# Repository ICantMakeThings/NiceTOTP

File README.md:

# NiceTOTP 

## Wiki

- [What is NiceTOTP?](#what-is-nicetotp)
- [But Why?](#but-why)
- [Hardware](#hardware-is)
- [Usage](#usage)
	- [UI](Docs/ui.md)
- [Installation](#installation)
	- [Standard installation](#standard-installation)
	- [Protected installation](#protected-installation)
- [More Info](#more-info)
- [Build protected from source](Docs/build-protected-from-source.md)

# What is NiceTOTP?

Time-based one-time password (TOTP). aka: 2FA! 
A alternetive to [Authy](https://www.authy.com/) / [Google Authenticator](https://play.google.com/store/apps/details?id=com.google.android.apps.authenticator2). 

Full offline, Air Gapped. And Standalone once all Keys have been added.

TOTP keys and other FS are stored in an AES-256-GCM encrypted vault, with a key derived from the passcode using PBKDF2-HMAC-SHA-256. Vaults use a random starting IV followed by monotonically increasing IVs.

A four-digit passcode is still vulnerable to offline guessing if an attacker extracts the flash. Use a longer, unpredictable numeric passcode; a lengt of 13 can make a attacker wait up to 8 years on the most common GPU* 

[Video here](https://www.youtube.com/watch?v=sLiadPXk7rc)

## But Why?? 

There are a few reasons why I made this device, mainly to lose dependence of my phone. But not just, What if your phone breaks, bricks, or something else? I rather have lots of devices that don't depend on eachother rather than a all in one for that reason, plus most "universal" stuff performs worse than a specific device for that single function. As of right now, I'd say it's almost complete (enough to daily drive), possibly a few more hardware security features, maybe UI polishing, fixing any bugs i haven't found yet and should be perfect. The cost is ~£6 excluding 3D printing.

## Hardware is:
+ Nice!Nano: [AliExpress Link](https://s.click.aliexpress.com/e/_omlmCuu)
+ DS3231 RTC: [AliExpress Link](https://s.click.aliexpress.com/e/_omVV4ia)
+ 0.96Inch Display: [AliExpress Link](https://s.click.aliexpress.com/e/_ooXwYgq)
+ 6*6 Silicone Switch: [AliExpress Link](https://s.click.aliexpress.com/e/_oDcs8Wa)
+ 3D [model](https://www.thingiverse.com/thing:7087241)

*Note: These are referral links. If you purchase through it, I earn a commission at no extra cost to you.*

# Usage
#### Use the [NiceTOTP-ConfiguratorNext](https://github.com/ICantMakeThings/NiceTOTP/releases)  (Firmware update doesnt work rn*)
#### or you can use serial commands:
- `setunixtime` example: `setunixtime 1751925355` 
- The first `setunixtime` stores the real time for future auto-calibration which after 30 days it will compensate for any drift in the DS3231.
- `manualcalibration <offset>` example: `manualcalibration 3` sets the DS3231 aging register from -128 to 127 and locks automatic calibration
- `lockcalibration` stops auto-calibration
- `unlockcalibration` turns back on auto-calibration
- `getcalibration` reports the aging offset, baseline timestamp, and lock state
- `clearcalibration` clears the aging correction and removes the stored calibration baseline
- `add <username> <base32secret>` example: `add test JBSWY3DPEHPK3PXP` ([Compare](https://totp.danhersam.com/?secret=JBSWY3DPEHPK3PXP))
- `list`
- `del <GetTheIDFromListCommand>` example: `del 1`
- `factoryreset` (Power cycle after)

# Installation

### Standard installation

If you don't care about proper security*, download the [NiceTOTP-ConfiguratorNext](https://github.com/ICantMakeThings/NiceTOTP/releases) and use the unsigned `NiceTOTP-V1x.uf2` firmware.

**Or if you just want to test the device without commiting to the protected bootloader / hassle with setting it up or not owning a ST-Link*

+ Or Drag and drop the .UF2 onto the nicenano drive when doubble clicking reset (short rst pin with usbc sheild tapping twice quickly)

### Protected installation
- Download `Signed.zip` from latest release, and follow
[Protected installation](Docs/build-protected-from-source.md) (Also includes installing from source)

# More Info

+ In 2 months the RTC drifted 8s forward. (Now there is a calibration feature, so should be better, to be commented on further.)

+ Battery seems to last about 1 year with a 1000mAh Battery.

+ Make sure not to let it discharge as it will go in a soft brick, to unbrick you just press rst 

#### GPU* 

- The algorythm is **50,000 PBKDF2** and the number is the expected value which is ½ of the worse-case scenario.
- It is based on cracking it with a NVIDIA GeForce RTX 3060 as its the most common GPU based on [Steam Hardware & Software Survey: August 2026.](https://store.steampowered.com/hwsurvey/En)
- It is recommended to have a pin of at least 13 Charicters
- You can have a look on [this webiste](https://jmrp.io/tools/pin-brute-force-calculator/) to test around different hardware, make sure PBKDF2 iterations is set to `50000`

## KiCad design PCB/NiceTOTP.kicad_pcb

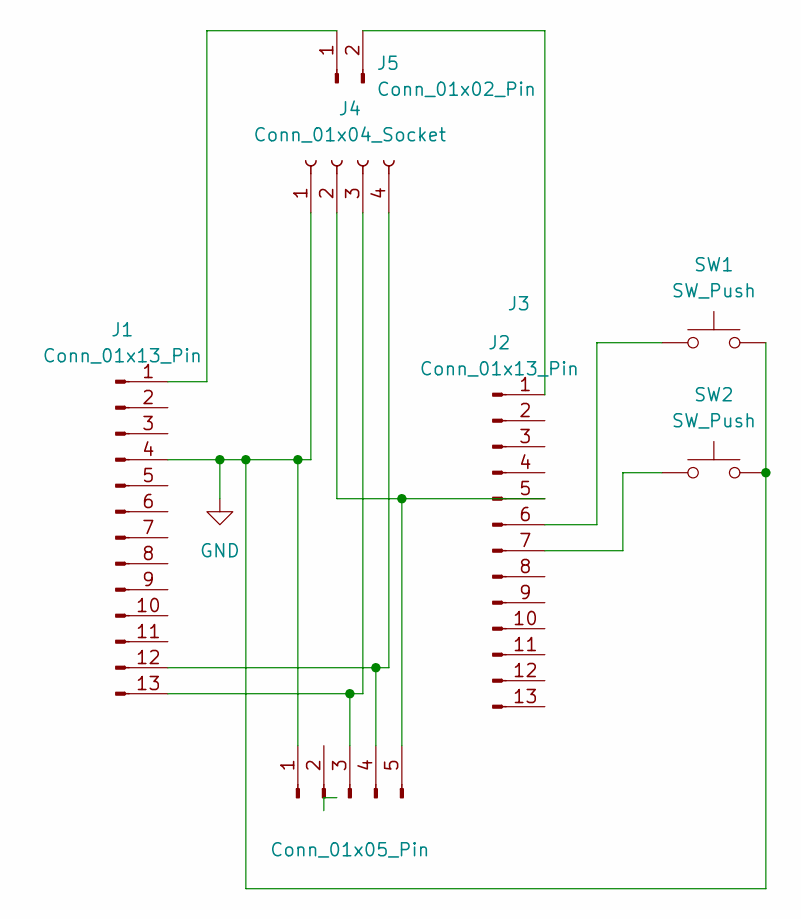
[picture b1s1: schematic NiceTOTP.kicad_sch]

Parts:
J1, J2: Conn_01x13_Pin; PinHeader_1x13_P2.54mm_Vertical
J3: Conn_01x05_Pin; PinHeader_1x05_P2.54mm_Vertical
J4: Conn_01x04_Socket; PinHeader_1x04_P2.54mm_Vertical
J5: Conn_01x02_Pin; PinHeader_1x02_P2.54mm_Vertical
SW1, SW2: SW_Push; SW_Push_1TS009xxxx-xxxx-xxxx_6x6x5mm

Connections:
GND: J1.4, J3.1, J4.1, SW1.2, SW2.2
unnamed: J1.1, J5.1
unnamed: J1.12, J3.4, J4.4
unnamed: J1.13, J3.3, J4.3
unnamed: J2.1, J5.2
unnamed: J2.5, J3.5, J4.2
unnamed: J2.6, SW1.1
unnamed: J2.7, SW2.1

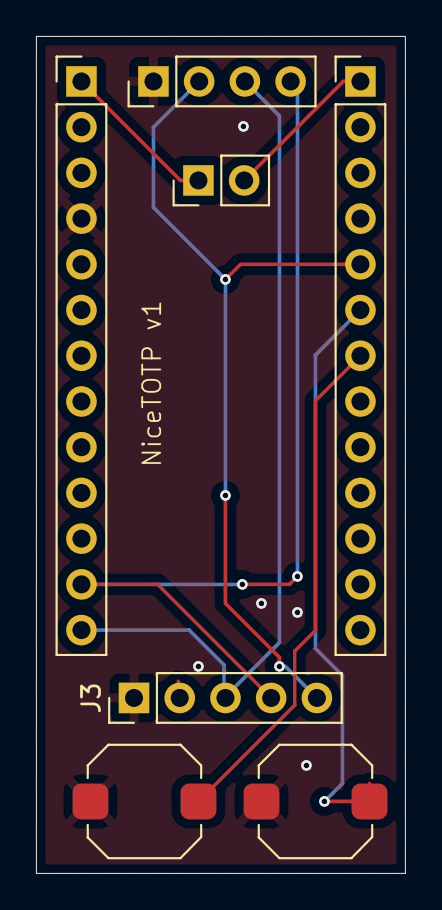
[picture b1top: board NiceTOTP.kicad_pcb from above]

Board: 2 copper layers, 20.5 x 46.5 mm, 7 parts (0 on the bottom side), 8 nets.

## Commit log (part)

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2025-07-08 Create LICENSE
2025-07-08 Revamp+Features
2025-07-09 Fixxed mental bugs
2025-07-09 Maybe fixxed??
2025-07-10 batt-animation-charging
2025-07-10 added dfu command
2025-07-10 MaybeDupeFix?
2025-07-10 swapped buttons
2025-07-10 commandye
2025-11-09 yeeeeeeeeees
2026-01-21 added dfu mode by holding both buttons at once for 10s or more
2026-01-21 added product name in usb
2026-03-25 Add Ko-fi username to FUNDING.yml
